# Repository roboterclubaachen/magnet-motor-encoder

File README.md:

# magnet-motor-encoder

## board-as5045b_rev10

### Motorencoder für axial befestigten diametralen Magneten

Motor-Encoder mit ams AS5045B.

Der AS5045B ist ein IC welcher die Ausrichtung eines über ihm befindlichen Magneten mit 12 Bit Auflösung erfasst.

An der Motorachse muss ein Ø 6 mm x 2.5 mm Magnet mit diametraler Orientierung befestigt werden, die zulässige Toleranz betrögt 0.1 mm.
Das Magnet ist exakt mittig über dem IC (welcher mittig auf der Platine platziert ist) ausgerichtet werden, der Toleranzbereich beträgt hier 0.25mm.

### Mechanische Dimensionen

Alle Angaben in Millimeter.

### Bauteile

Anzahl | Bauteil              | Bezeichnung / MPN
------ | -------------------- | -----------------------
1      | Magnetsensor IC      | AS5045B-ASSM
1      | Stecker Vorderseite  | [JST GH SM05B-GHS](https://www.digikey.de/product-detail/de/jst-sales-america-inc/SM05B-GHS-TB-LF-SN/455-1567-1-ND/807835) (1.25mm)
1      | Stecker Rückseite    | [JST GH BM05B-GHS](https://www.digikey.de/product-detail/de/jst-sales-america-inc/BM05B-GHS-TBT-LF-SN-N/455-1581-1-ND/807849) (1.25mm)
1      | LED Rot              | Bauform 0603
1      | LED Gelb             | Bauform 0603
2      | Vorwiderstand LED    | Bauform 0402
3 or 4 | Null-Ohm-Widerstand  | Bauform 0402
2      | Kondensator          | 2,2µF, >6,3V, X7R, Bauform 0603

### Stecker

Auf der Platine sind zwei 5-polige [JST GH](https://jst.de/product-family/show/89/gh) Stecker vorgesehen, welche Alternative bestückt werden können.
Der Stecker auf Vorderseite der Platine (wo auch der Sensor sitzt) bietet einen horizontalen Kabelausgang während auf der Rückseite ein vertikaler Kabelausgang vorgesehen ist.

Das Pinout beider Stecker ist identisch.

Pin | ABI-Interface | Serielles Interface
--- | ------------- | -------------------
 1  | A             | Data Out
 2  | +5V oder +3V3 | +5V oder +3V3
 3  | B             | Clock
 4  | I             | Chip Select (inverted)
 5  | GND           | GND

### Optionen / Konfiguration

#### Versorgungsspannung

Es sind sowohl 3,3V als auch 5V Versorgungsspannung möglich.
Die Versorgungsspannung muss mittels des einzigen Null-Ohm-Widerstands auf der Vorderseite (Beschriftung "3V") konfiguriert werden.

Spannung     | Null-Ohm-Widerstands (Beschriftung "3V")
------------ | ----------------------------------------
4,5V .. 5,5V | Nicht bestückt
3,0V .. 3,6V | Bestückt

#### Interface

Mittels Null-Ohm-Widerständen können wahlweise das ABI- oder das serielle Interface aktiviert werden.

Zur Nutzung des ABI-Interfaces müssen die drei Null-Ohm-Widerstände innerhalb der blauen Markierung eingelötet werden.

Zur Aktivierung des seriellen Interfaces müssen die drei Null-Ohm-Widerstände innerhalb der roten Markierung eingelötet werden.

### Diagnose LEDs
* Rote und gelbe LEDs: Magnetfeldstärke
  * Aus: optimaler Betrieb
  * Gelb leuchtet: schwache Magnetfeldstärke, Magnet näher an IC platzieren.
  * Rot leuchtet: starke Magnetfeldstärke, Magnet weiter vom IC entfernt platzieren.
  * Rot und Gelb leuchten gleichzeitig: zu starkes oder zu schwaches Magnetfeld, keine zuverlässiger Betrieb möglich.

## board-as5045b

### Motorencoder für axial befestigten diametralen Magneten

Siehe [oben](#board-as5045b_rev10).

Die Platine ist hat exakt 22mm Durchmesser und sollte damit zu den *Namika* Motoren (ebenfalls 22mm Durchmesser) passen.
Das Magnet ist exakt mittig über dem IC, welcher mittig auf der Platine platziert ist, ausgerichtet werden.

### Diagnose LEDs
* Blaue LED: Power
* Rote und gelbe LEDs: Magnetfeldstärke
  * Aus: optimaler Betrieb
  * Gelb leuchtet: schwache Magnetfeldstärke, Magnet näher an IC platzieren.
  * Rot und Gelb leuchten: zu starkes oder zu schwaches Magnetfeld, keine zuverlässiger Betrieb möglich.

## board-as5304

### Motorencoder für axial befestigten mehrpoligen Ringmagneten

Motor-Encoder mit **ams** AS5304(A).

Der AS5304 ist ein IC welcher die Bewegung eines über ihm befindlichen mehrpoligen Magneten mit 160 Schritten pro Magnetpolpaar erfasst.
Die Platine ist hat etwa 12 mm Höhe und 39 mm Breite sowie ein 2mm Loch zu Ausrichtung über der Motorwelle.
Bei Bedarf kann dieses Loch aufgebohrt werden, in der Umgebung sind keine Leiterbahnen und kein Kupfer vorhanden.

An der Motorachse muss ein Ringmagnet mit 24 mm Innendurchmesser und 32 mm Außendurchmesser (-> MIttendurchmesser 28 mm) mittels eines nicht ferromagmetischen Werkstoffs befestigt werden.
Das Sensorarray im IC befindet sich exakt 28 mm vom Loch für die Motorachse entfernt, sodass die Platine bei Verwendung des oben genannten Magneten nur an der Motorachse und mit ca. 0.5 mm zum Ringmagnet ausgerichtet werden muss.

### Diagnose
* Blaue LED: Power
* Am Testpoint **AO** kann eine von der Magnetfeldstärke abhängige Spannung (gegen Testpoint **GND**) gemessen werden.

## License

Copyright Raphael Lehmann 2016-2019

Licensed under CERN OHL v.1.2

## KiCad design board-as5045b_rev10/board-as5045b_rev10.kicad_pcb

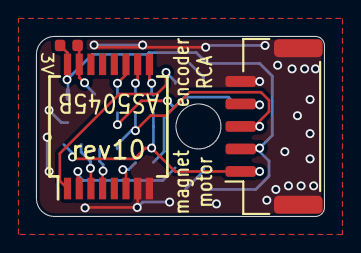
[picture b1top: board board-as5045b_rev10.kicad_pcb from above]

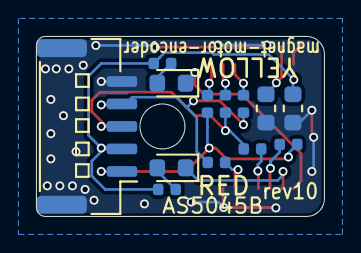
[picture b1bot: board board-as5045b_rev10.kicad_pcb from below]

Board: 2 copper layers, 16.0 x 10.0 mm, 16 parts (13 on the bottom side), 16 nets.

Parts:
C1, C2: 1µ 10V; C_0603_1608Metric
D1: YEL; LED_0603_1608Metric
D2: RED; LED_0603_1608Metric
J1: Connector_JST:JST_GH_BM05B-GHS-TBT_1x05-1MP_P1.25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; JST_GH_BM05B-GHS-TBT_1x05-1MP_P1.25mm_Vertical
J2: Connector_JST:JST_GH_SM05B-GHS-TB_1x05-1MP_P1.25m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; JST_GH_SM05B-GHS-TB_1x05-1MP_P1.25mm_Horizontal
JP1: 3V3; R_0402_1005Metric
R1, R2: 2k; R_0402_1005Metric
R3, R4, R5: 0; R_0402_1005Metric
R6, R7, R8: DNP; R_0402_1005Metric
U1: AS5045B; SSOP-16_5.3x6.2mm_P0.65mm

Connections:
+3V3: C2.1, JP1.2, U1.15
+5V: C1.1, J1.2, J2.2, JP1.1, R1.2, R2.2, U1.16
GND: C1.2, C2.2, J1.5, J1.MP, J2.5, J2.MP, U1.7, U1.8
unnamed: D1.1, U1.1
unnamed: D1.2, R1.1
unnamed: D2.1, U1.2
unnamed: D2.2, R2.1
unnamed: J1.1, J2.1, R3.1, R6.1
unnamed: J1.3, J2.3, R4.1, R7.1
unnamed: J1.4, J2.4, R5.1, R8.1
unnamed: R3.2, U1.3
unnamed: R4.2, U1.4
unnamed: R5.2, U1.6
unnamed: R6.2, U1.9
unnamed: R7.2, U1.10
unnamed: R8.2, U1.11

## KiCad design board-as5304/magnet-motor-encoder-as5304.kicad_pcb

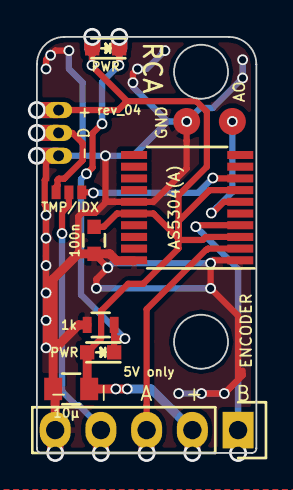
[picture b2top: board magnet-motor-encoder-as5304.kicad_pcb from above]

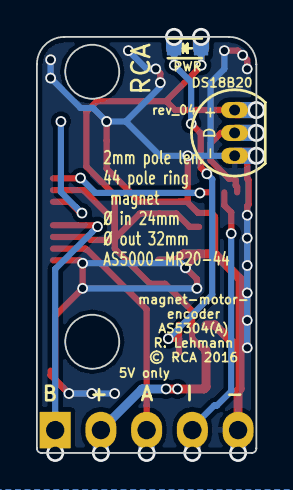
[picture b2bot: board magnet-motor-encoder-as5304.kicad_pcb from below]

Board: 2 copper layers, 12.2 x 23.1 mm, 12 parts (2 on the bottom side), 9 nets.

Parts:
C1: 100n; C_0603
C2: 10µ; C_0805
D1, D2, D2#2: PWR; LED_0603
JP1: ENCODER; Pin_Header_Straight_1x05
R1: 1k; R_0603
SJ1: TMP/IDX; S_JUMPER_3
U1: DS18B20; TO-92_Inline_Narrow_Oval
U2: AS5304(A); TSSOP-20_4.4x6.5mm_Pitch0.65mm
W1: GND; Measurement_Point_Round-SMD-Pad_Small
W2: AO; Measurement_Point_Round-SMD-Pad_Small

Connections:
+5V: C1.1, C2.1, D1.2, D2.2, D2#2.2, JP1.2, U1.3, U2.3, U2.7, U2.16
/A: JP1.3, U2.2
/AO: U2.6, W2.1
/B: JP1.1, U2.4
/IDX: SJ1.3, U2.8
/LED: D1.1, D2.1, D2#2.1, R1.1
/TMP: SJ1.1, U1.2
/TMP_IDX: JP1.4, SJ1.2
GND: C1.2, C2.2, JP1.5, R1.2, U1.1, U2.1, U2.15, U2.20, W1.1

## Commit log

2016-07-04 add gitignore
2016-07-04 inital board schematic and layout
2016-07-04 board layout and silkscreen
2016-07-04 board: silkscreen and ground vias
2016-07-04 board; adjust silkscreen
2016-07-04 add README
2016-07-06 board: add 1wire eagle library (LGPL)
2016-07-06 board: add DS18B20 temperature sensor (optional/uses encoder index pin signal)
2016-07-06 board: adjust silk screen; add rev2 label
2016-07-06 board: some minor fixes and improvements; rev3 label
2016-07-09 added magnet-motor-encoder-as5304 schematic (kicad) and kicad libs for solder jumper, as5304 and rca encoder psk
2016-07-09 remove kicad lib cache / extend gitignore
2016-07-09 board as5304: add AO and GND test points
2016-07-10 board AS5304: add Power LED
2016-07-10 KiCad lib solder jumper: Pins changed to passive
2016-07-10 board as5304: modified solder jumper; ERC passed
2016-07-10 kicad lib: add open-project kicad footprint lib
2016-07-10 board as5304: footprints selected, netlist created
2016-07-10 board as5304: add test point library; replace measurement point footprint
2016-07-10 board as5304: add lib bjh-kicad-mountingholes-fp
2016-07-10 board as5304: create pcb layout
2016-07-10 board as5304: remove generated netlist file
2016-07-10 board as5304: replaced absolute libary paths
2016-07-10 board as5304: named signals in schematic
2016-07-10 board as5304: fix component values
2016-07-10 board as5304: finish pcb layout and silkscreen
2016-07-10 board as5045b: integrate mounting holes in board outline
2016-07-10 renamed board directories
2016-07-10 add as5304 board and images to README
2016-07-26 board as5304: rearrange components
2016-07-31 board as5304: replace bjh-kicad-mountingholes-fp with own fork
2016-07-31 board as5304: finish pcb layout and silkscreen for rev_02
2016-07-31 updated documentation for as5304 rev_02
2016-07-31 add CERN OHL v.1.2 license
2016-08-09 board as5304: replace most 0805 Rs and Cs with 0603 packages
2016-08-09 board as5304: update README images
2016-09-01 board as5045b: new board shape (imported from 3d-model/solidworks); rev4 tag
2016-09-01 board as5304: new board shape (imported from 3d-model/solidworks); rev_04 tag
2016-09-20 board as5045b: moved backside resistors; new rev4 tag
2016-10-12 board as5045b: add missing CSn pulldown resistor; new rev5 tag
2019-08-16 Add datasheet PDFs (No longer available on the AMS website)
2019-08-16 Add new board as5045b_rev10

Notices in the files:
board-as5304/magnet-motor-encoder-as5304.kicad_pcb:
© RCA 2016
